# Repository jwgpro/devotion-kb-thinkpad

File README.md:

# Devotion keyboard: ThinkPad

STM32-based USB controller boards intended for old ThinkPad keyboards with the same 40-pin connector; T60, T420, etc.

`kb-only`: Simple board connecting all pins of a 40-pin keyboard connector (0.5 mm pitch) to STM32 I/O pins. No trackpoint supported. Could be used for any keyboard conforming to the same FFC/FPC connector. [QMK branch](https://github.com/jwgpro/qmk_firmware/tree/devotion-kb-thinkpad_kb-only)

`full`: **(TODO)** With trackpoint support. For specific keyboards only.

Other variants planned.

Licence: CERN-OHL-S-2.0

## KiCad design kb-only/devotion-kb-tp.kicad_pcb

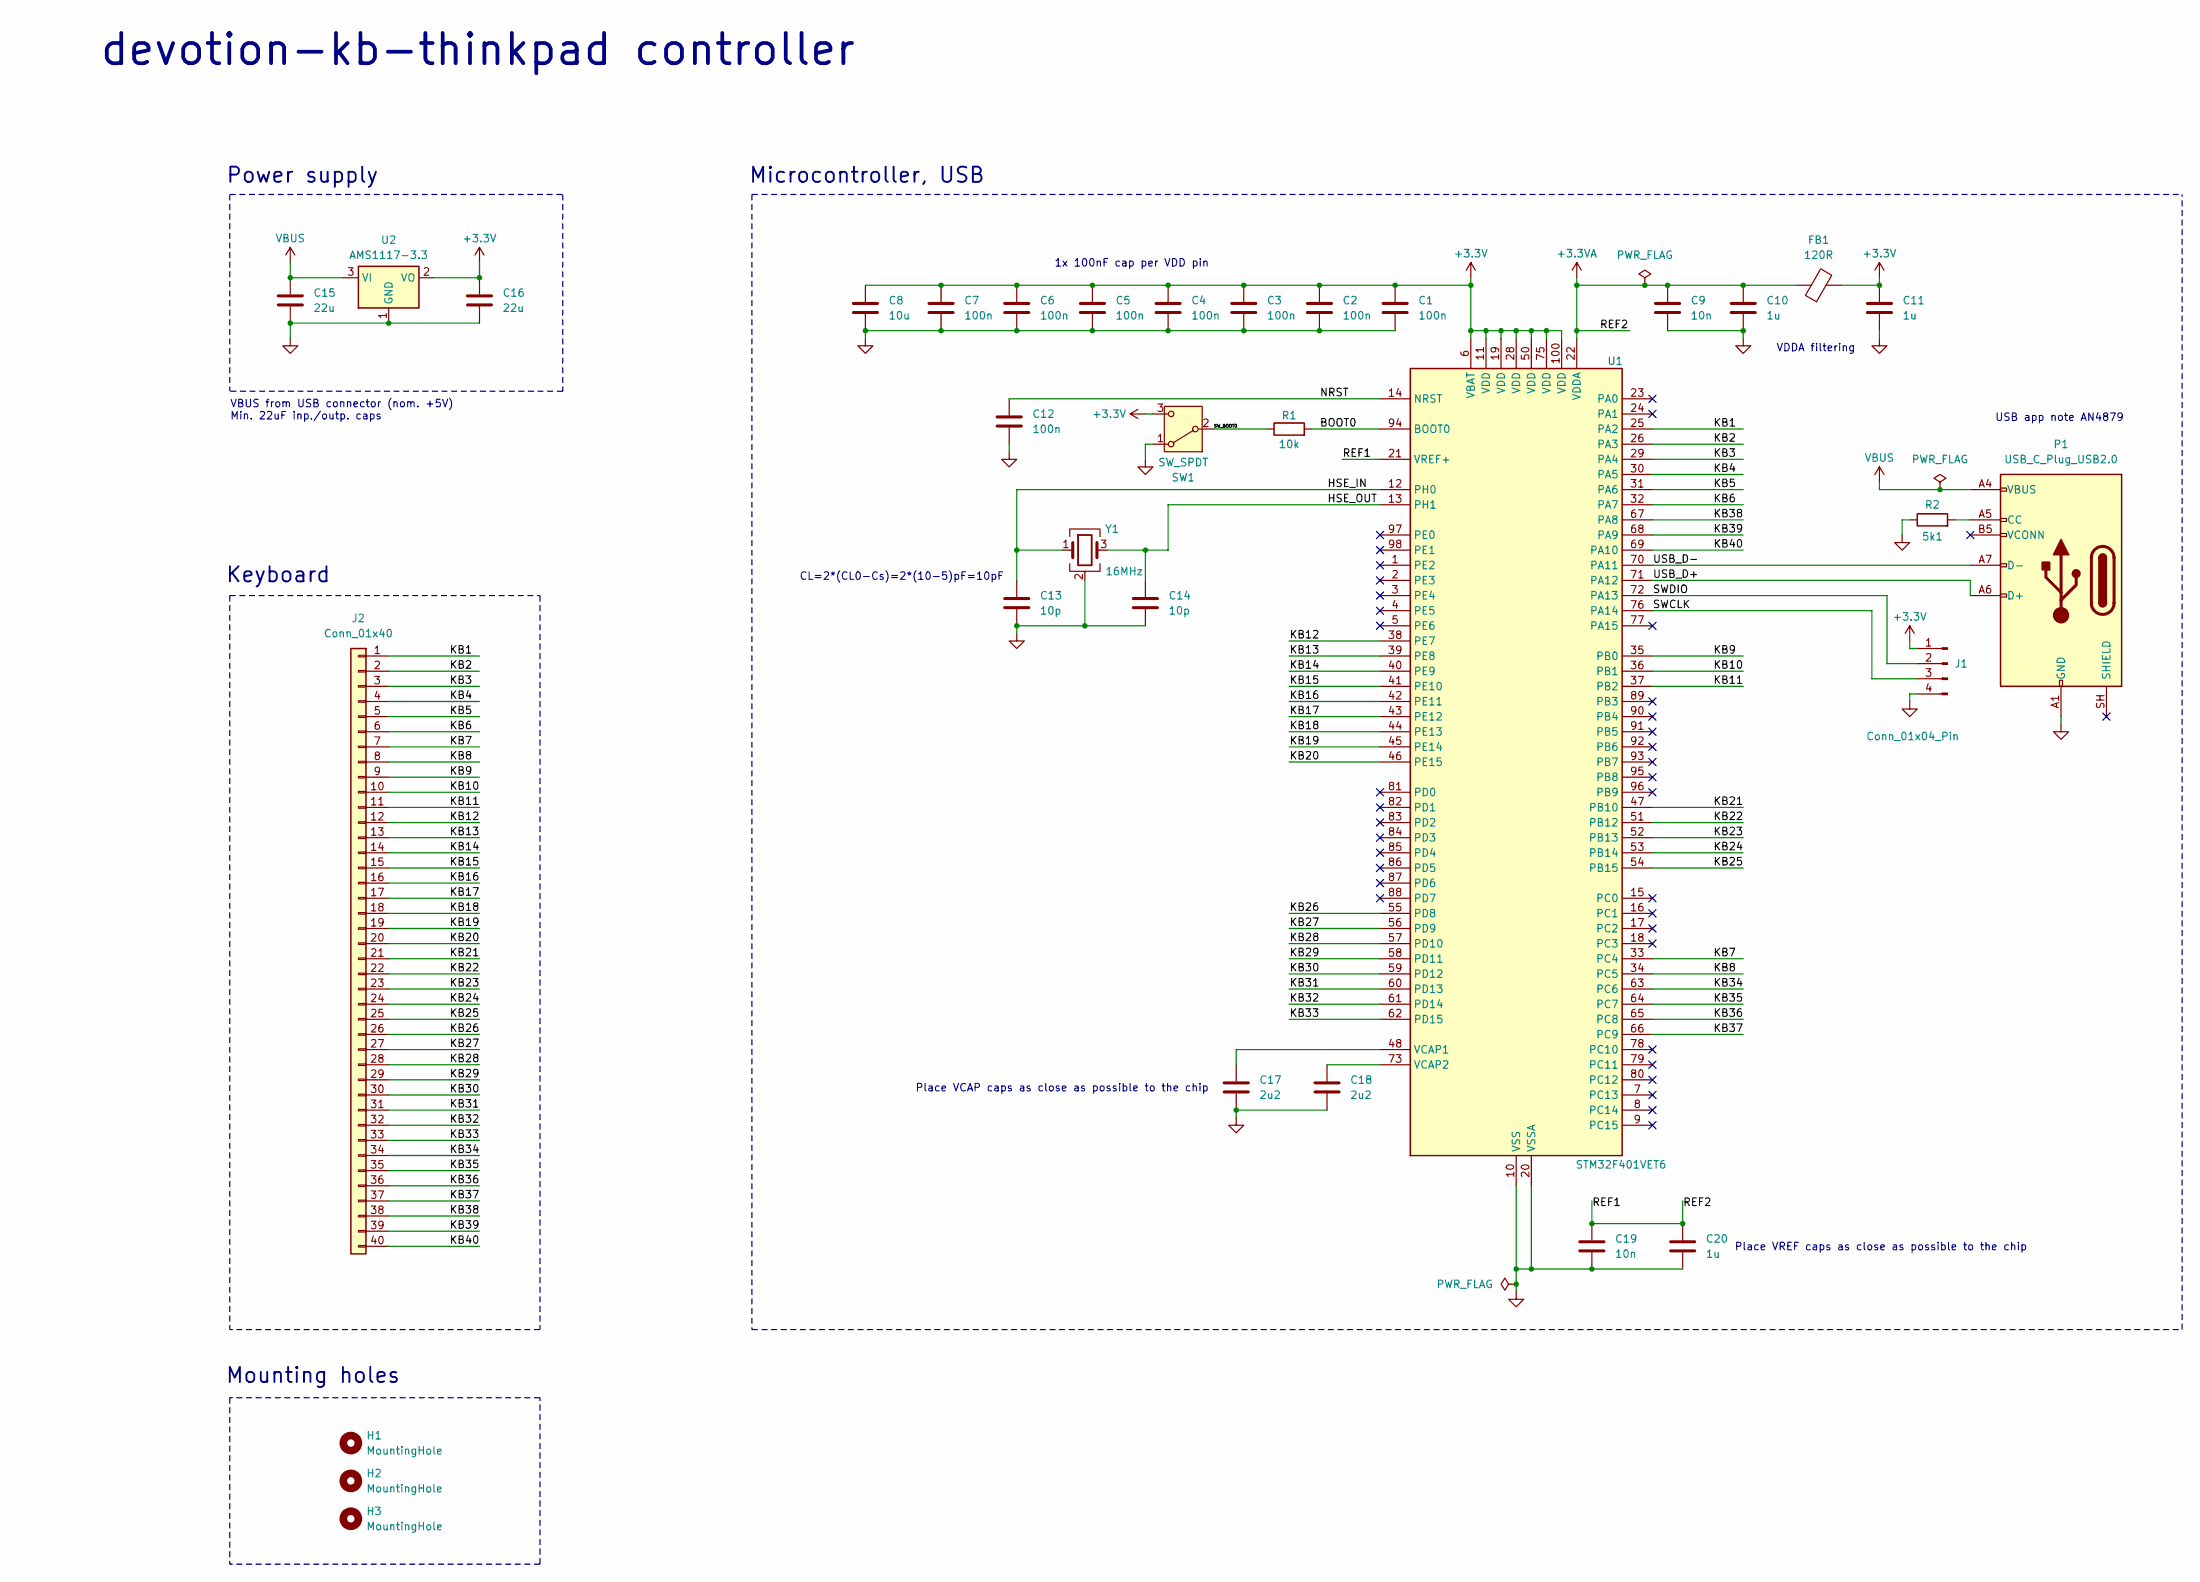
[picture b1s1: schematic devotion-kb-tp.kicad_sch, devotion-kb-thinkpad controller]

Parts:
C1, C2, C3, C4, C5, C6, C7, C12: 100n; C_0402_1005Metric
C8: 10u; C_0603_1608Metric
C9, C19: 10n; C_0402_1005Metric
C10, C11, C20: 1u; C_0402_1005Metric
C13, C14: 10p; C_0402_1005Metric
C15, C16: 22u; C_0805_2012Metric
C17, C18: 2u2; C_0402_1005Metric
FB1: 120R; L_0603_1608Metric
H1, H2, H3: MountingHole; MountingHole_3.5mm
J1: Conn_01x04_Pin; PinHeader_1x04_P2.54mm_Vertical
J2: Conn_01x40; Hirose_FH12-40S-0.5SH_1x40-1MP_P0.50mm_Horizontal
P1: USB_C_Plug_USB2.0; USB_C_Receptacle_HRO_TYPE-C-31-M-12
R1: 10k; R_0402_1005Metric
R2: 5k1; R_0402_1005Metric
SW1: SW_SPDT; SW_SPDT_PCM12
U1: STM32F401VET6; LQFP-100_14x14mm_P0.5mm
U2: AMS1117-3.3; SOT-223-3_TabPin2
Y1: 16MHz; Crystal_SMD_3225-4Pin_3.2x2.5mm

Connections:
+3.3V: C1.1, C2.1, C3.1, C4.1, C5.1, C6.1, C7.1, C8.1, C11.1, C16.1, FB1.2, J1.1, SW1.3 (C), U1.6 (VBAT), U1.11 (VDD), U1.19 (VDD), U1.28 (VDD), U1.50 (VDD), U1.75 (VDD), U1.100 (VDD), U2.2 (VO)
+3.3VA: C9.1, C10.1, C19.1, C20.1, FB1.1, U1.21 (VREF+), U1.22 (VDDA)
/BOOT0: R1.2, U1.94 (BOOT0)
/HSE_IN: C13.1, U1.12 (PH0), Y1.1
/HSE_OUT: C14.1, U1.13 (PH1), Y1.3
/KB1: J2.1, U1.25 (PA2)
/KB2: J2.2, U1.26 (PA3)
/KB3: J2.3, U1.29 (PA4)
/KB4: J2.4, U1.30 (PA5)
/KB5: J2.5, U1.31 (PA6)
/KB6: J2.6, U1.32 (PA7)
/KB7: J2.7, U1.33 (PC4)
/KB8: J2.8, U1.34 (PC5)
/KB9: J2.9, U1.35 (PB0)
/KB10: J2.10, U1.36 (PB1)
/KB11: J2.11, U1.37 (PB2)
/KB12: J2.12, U1.38 (PE7)
/KB13: J2.13, U1.39 (PE8)
/KB14: J2.14, U1.40 (PE9)
/KB15: J2.15, U1.41 (PE10)
/KB16: J2.16, U1.42 (PE11)
/KB17: J2.17, U1.43 (PE12)
/KB18: J2.18, U1.44 (PE13)
/KB19: J2.19, U1.45 (PE14)
/KB20: J2.20, U1.46 (PE15)
/KB21: J2.21, U1.47 (PB10)
/KB22: J2.22, U1.51 (PB12)
/KB23: J2.23, U1.52 (PB13)
/KB24: J2.24, U1.53 (PB14)
/KB25: J2.25, U1.54 (PB15)
/KB26: J2.26, U1.55 (PD8)
/KB27: J2.27, U1.56 (PD9)
/KB28: J2.28, U1.57 (PD10)
/KB29: J2.29, U1.58 (PD11)
/KB30: J2.30, U1.59 (PD12)
/KB31: J2.31, U1.60 (PD13)
/KB32: J2.32, U1.61 (PD14)
/KB33: J2.33, U1.62 (PD15)
/KB34: J2.34, U1.63 (PC6)
/KB35: J2.35, U1.64 (PC7)
/KB36: J2.36, U1.65 (PC8)
/KB37: J2.37, U1.66 (PC9)
/KB38: J2.38, U1.67 (PA8)
/KB39: J2.39, U1.68 (PA9)
/KB40: J2.40, U1.69 (PA10)
/NRST: C12.1, U1.14 (NRST)
/SWCLK: J1.3, U1.76 (PA14)
/SWDIO: J1.2, U1.72 (PA13)
/SW_BOOT0: R1.1, SW1.2 (B)
/USB_D+: P1.A6 (D+), U1.71 (PA12)
/USB_D-: P1.A7 (D-), U1.70 (PA11)
GND: C1.2, C2.2, C3.2, C4.2, C5.2, C6.2, C7.2, C8.2, C9.2, C10.2, C11.2, C12.2, C13.2, C14.2, C15.2, C16.2, C17.2, C18.2, C19.2, C20.2, J1.4, P1.A1 (GND), P1.A12 (GND), P1.B1 (GND), P1.B12 (GND), R2.1, SW1.1 (A), U1.10 (VSS), U1.20 (VSSA), U1.27 (VSS), U1.49 (VSS), U1.74 (VSS), U1.99 (VSS), U2.1 (GND), Y1.2 (G), Y1.4 (G)
unnamed: P1.A5 (CC), R2.2
unnamed: C17.1, U1.48 (VCAP1)
unnamed: C18.1, U1.73 (VCAP2)
VBUS: C15.1, P1.A4 (VBUS), P1.A9 (VBUS), P1.B4 (VBUS), P1.B9 (VBUS), U2.3 (VI)

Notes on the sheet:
Power supply
Keyboard
CL=2*(CL0-Cs)=2*(10-5)pF=10pF
1x 100nF cap per VDD pin
Microcontroller, USB
USB app note AN4879
VBUS from USB connector (nom. +5V) Min. 22uF inp./outp. caps
Place VREF caps as close as possible to the chip
VDDA filtering
Place VCAP caps as close as possible to the chip
devotion-kb-thinkpad controller
Mounting holes

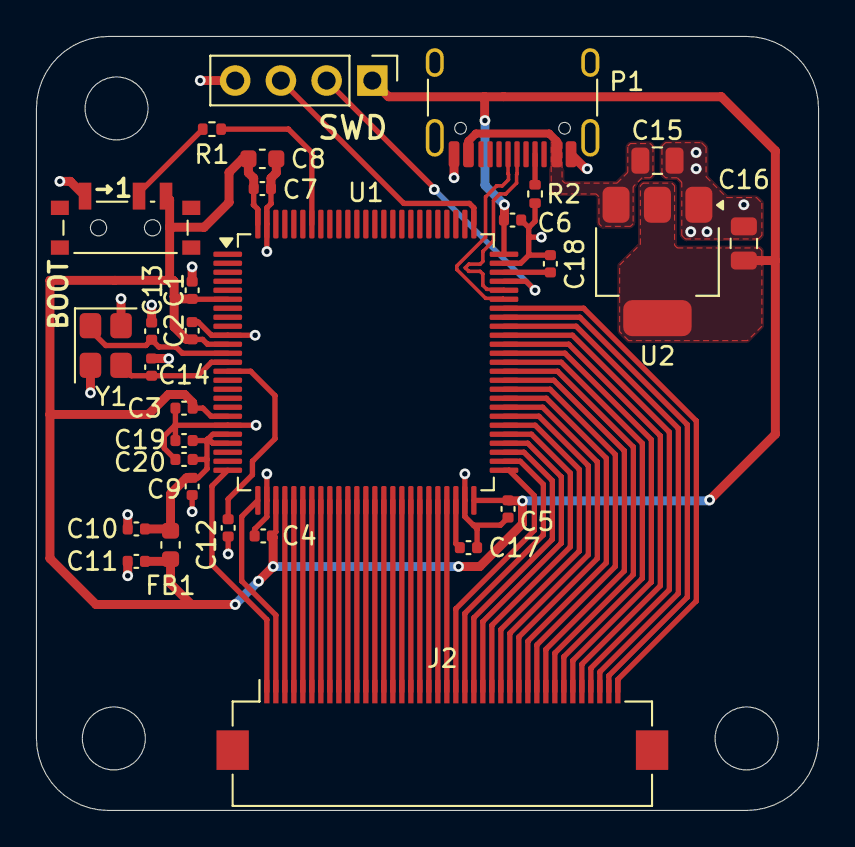
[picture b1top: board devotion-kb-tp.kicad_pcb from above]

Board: 2 copper layers, 43.5 x 43.0 mm, 33 parts (0 on the bottom side), 56 nets.

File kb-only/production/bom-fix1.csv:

Designator,Footprint,Quantity,Value,LCSC Part #
"C1, C12, C2, C3, C4, C5, C6, C7",402,8,100n,C2168432
"C10, C11, C20",402,3,1u,C2649511
"C13, C14",402,2,10p,C22937232
"C15, C16",805,2,22u,C318688
"C17, C18",402,2,2u2,C307419
"C19, C9",402,2,10n,C437525
C8,603,1,10u,C77040
FB1,603,1,120R,C85831
J1,PinHeader_1x04_P2.54mm_Vertical,1,Conn_01x04_Pin,
J2,Hirose_FH12-40S-0.5SH_1x40-1MP_P0.50mm_Horizontal,1,Conn_01x40,C202114
P1,USB_C_Receptacle_HRO_TYPE-C-31-M-12,1,USB_C_Plug_USB2.0,C963370
R1,402,1,10k,C2989267
R2,402,1,5k1,C53109434
SW1,SW_SPDT_PCM12,1,SW_SPDT,C221841
U1,LQFP-100_14x14mm_P0.5mm,1,STM32F401VET6,C1337110
U2,SOT-223-3_TabPin2,1,AMS1117-3.3,C6186
Y1,Crystal_SMD_3225-4Pin_3.2x2.5mm,1,16MHz,C112972

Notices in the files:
kb-only/devotion-kb-tp.kicad_pcb:
Licensed under CERN-OHL-S-2.0
